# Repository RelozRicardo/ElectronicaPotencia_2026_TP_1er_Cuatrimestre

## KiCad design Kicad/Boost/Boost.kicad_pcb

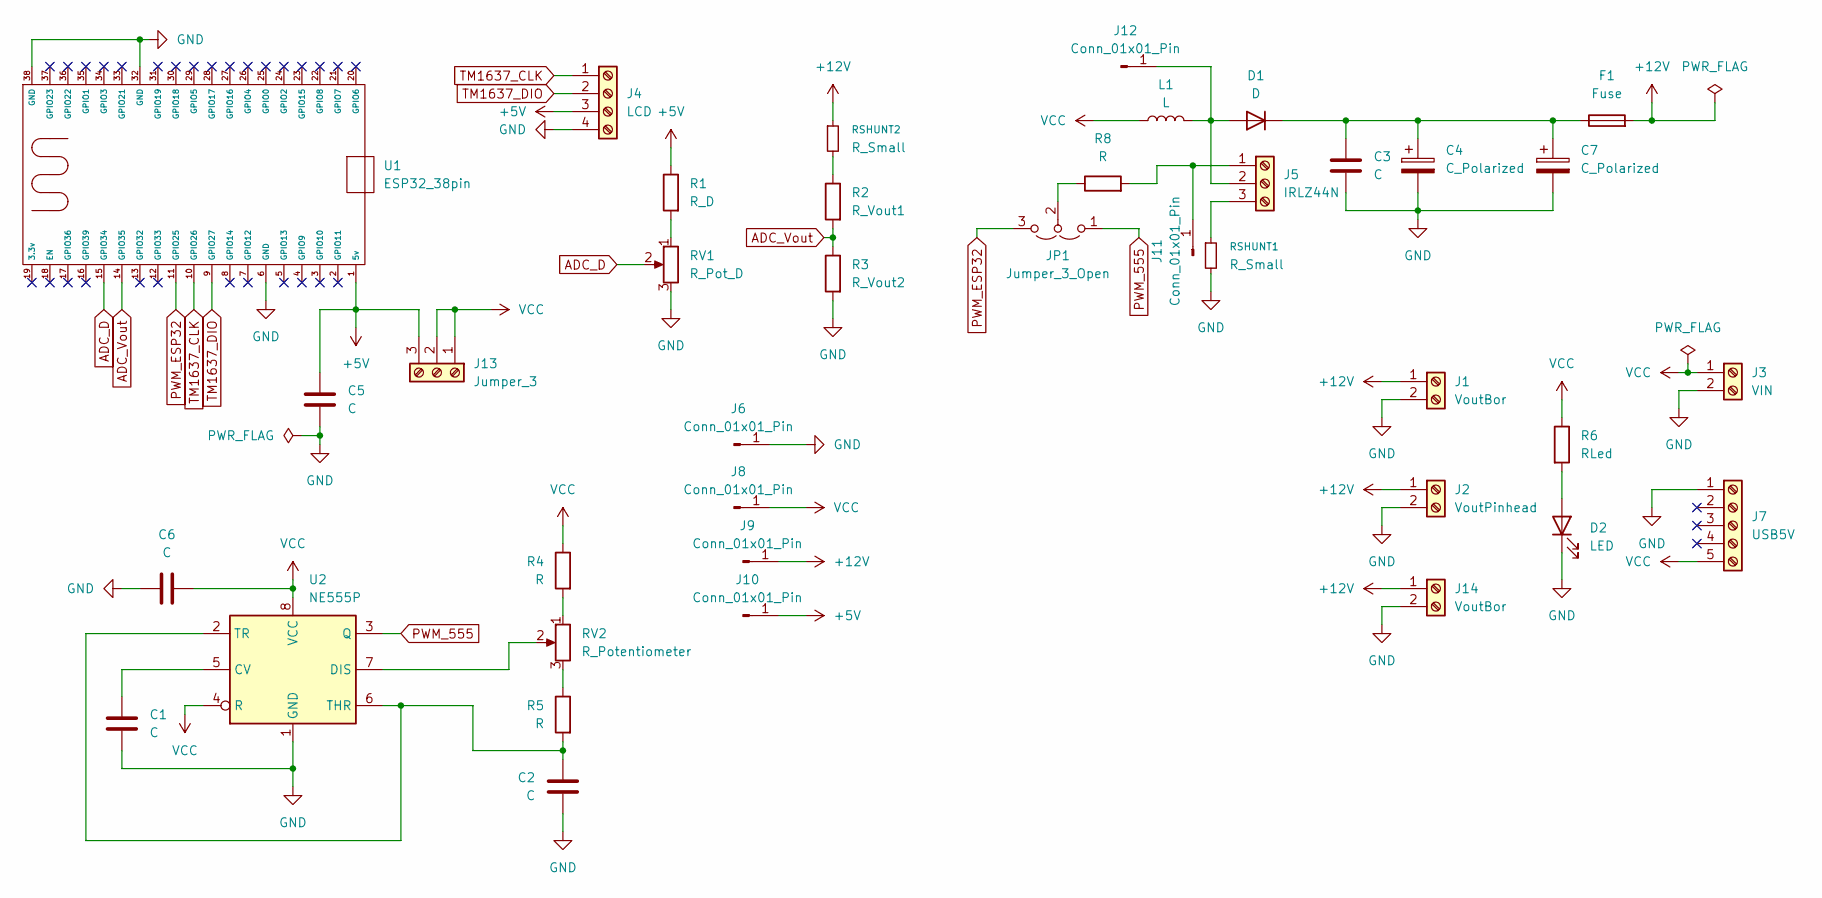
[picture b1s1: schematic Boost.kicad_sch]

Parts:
C1, C2, C3, C5, C6: C; C_Disc_D3.8mm_W2.6mm_P2.50mm
C4, C7: C_Polarized; CP_Radial_D6.3mm_P2.50mm
D1: D; D_DO-201_P12.70mm_Horizontal
D2: LED; LED_D5.0mm
F1: Fuse; Fuse_Bourns_MF-RG400
J1, J14: VoutBor; PhoenixContact_MSTBA_2,5_2-G-5,08_1x02_P5.08mm_Horizontal
J2: VoutPinhead; Molex_KK-254_AE-6410-02A_1x02_P2.54mm_Vertical
J3: VIN; PhoenixContact_MSTBA_2,5_2-G-5,08_1x02_P5.08mm_Horizontal
J4: LCD; PinHeader_1x04_P2.54mm_Vertical
J5: IRLZ44N; TerminalBlock_Xinya_XY308-2.54-3P_1x03_P2.54mm_Horizontal
J6, J8, J9, J10, J11, J12: Conn_01x01_Pin; PinHeader_1x01_P2.54mm_Vertical
J7: USB5V; MicroUsb_Arduino
J13: Jumper_3; PinHeader_1x03_P2.54mm_Vertical
JP1: Jumper_3_Open; PinHeader_1x03_P2.54mm_Vertical
L1: L; Inductor_T94_Vertical
R1: R_D; R_Axial_DIN0207_L6.3mm_D2.5mm_P7.62mm_Horizontal
R2: R_Vout1; R_Axial_DIN0207_L6.3mm_D2.5mm_P7.62mm_Horizontal
R3: R_Vout2; R_Axial_DIN0207_L6.3mm_D2.5mm_P7.62mm_Horizontal
R4, R5, R8: R; R_Axial_DIN0207_L6.3mm_D2.5mm_P7.62mm_Horizontal
R6: RLed; R_Axial_DIN0207_L6.3mm_D2.5mm_P7.62mm_Horizontal
RSHUNT1, RSHUNT2: R_Small; R_2010_5025Metric_Pad1.40x2.65mm_HandSolder
RV1: R_Pot_D; Potentiometer_ACP_CA9-H2,5_Horizontal
RV2: R_Potentiometer; Potentiometer_ACP_CA9-H2,5_Horizontal
U1: ESP32_38pin; ESP32Wroom32_38Pines
U2: NE555P; DIP-8_W7.62mm

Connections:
+5V: C5.1, J4.3, J10.1 (Pin_1_1), J13.3, R1.1, U1.1 (5v)
+12V: F1.2, J1.1, J2.1, J9.1 (Pin_1_1), J14.1, RSHUNT2.1
ADC_D: RV1.2, U1.15 (GPIO34)
ADC_Vout: R2.2, R3.1, U1.14 (GPIO35)
GND: C1.2, C2.2, C3.2, C4.2, C5.2, C6.1, C7.2, D2.1 (K), J1.2, J2.2, J3.2, J4.4, J6.1 (Pin_1_1), J7.1, J14.2, R3.2, RSHUNT1.2, RV1.3, U1.6 (GND), U1.32 (GND), U1.38 (GND), U2.1 (GND)
unnamed: D1.2 (A), J5.2, J12.1 (Pin_1_1), L1.2
unnamed: C3.1, C4.1, C7.1, D1.1 (K), F1.1
unnamed: D2.2 (A), R6.2
unnamed: J5.3, RSHUNT1.1
unnamed: J5.1, J11.1 (Pin_1_1), R8.2
unnamed: JP1.2 (C), R8.1
unnamed: R1.2, RV1.1
unnamed: R2.1, RSHUNT2.2
unnamed: R4.2, RV2.1
unnamed: R5.1, RV2.3
unnamed: C1.1, U2.5 (CV)
unnamed: RV2.2, U2.7 (DIS)
unnamed: C2.1, R5.2, U2.2 (TR), U2.6 (THR)
PWM_555: JP1.1 (A), U2.3 (Q)
PWM_ESP32: JP1.3 (B), U1.11 (GPIO25)
TM1637_CLK: J4.1, U1.10 (GPIO26)
TM1637_DIO: J4.2, U1.9 (GPIO27)
VCC: C6.2, J3.1, J7.5, J8.1 (Pin_1_1), J13.1, J13.2, L1.1, R4.1, R6.1, U2.4 (R), U2.8 (VCC)

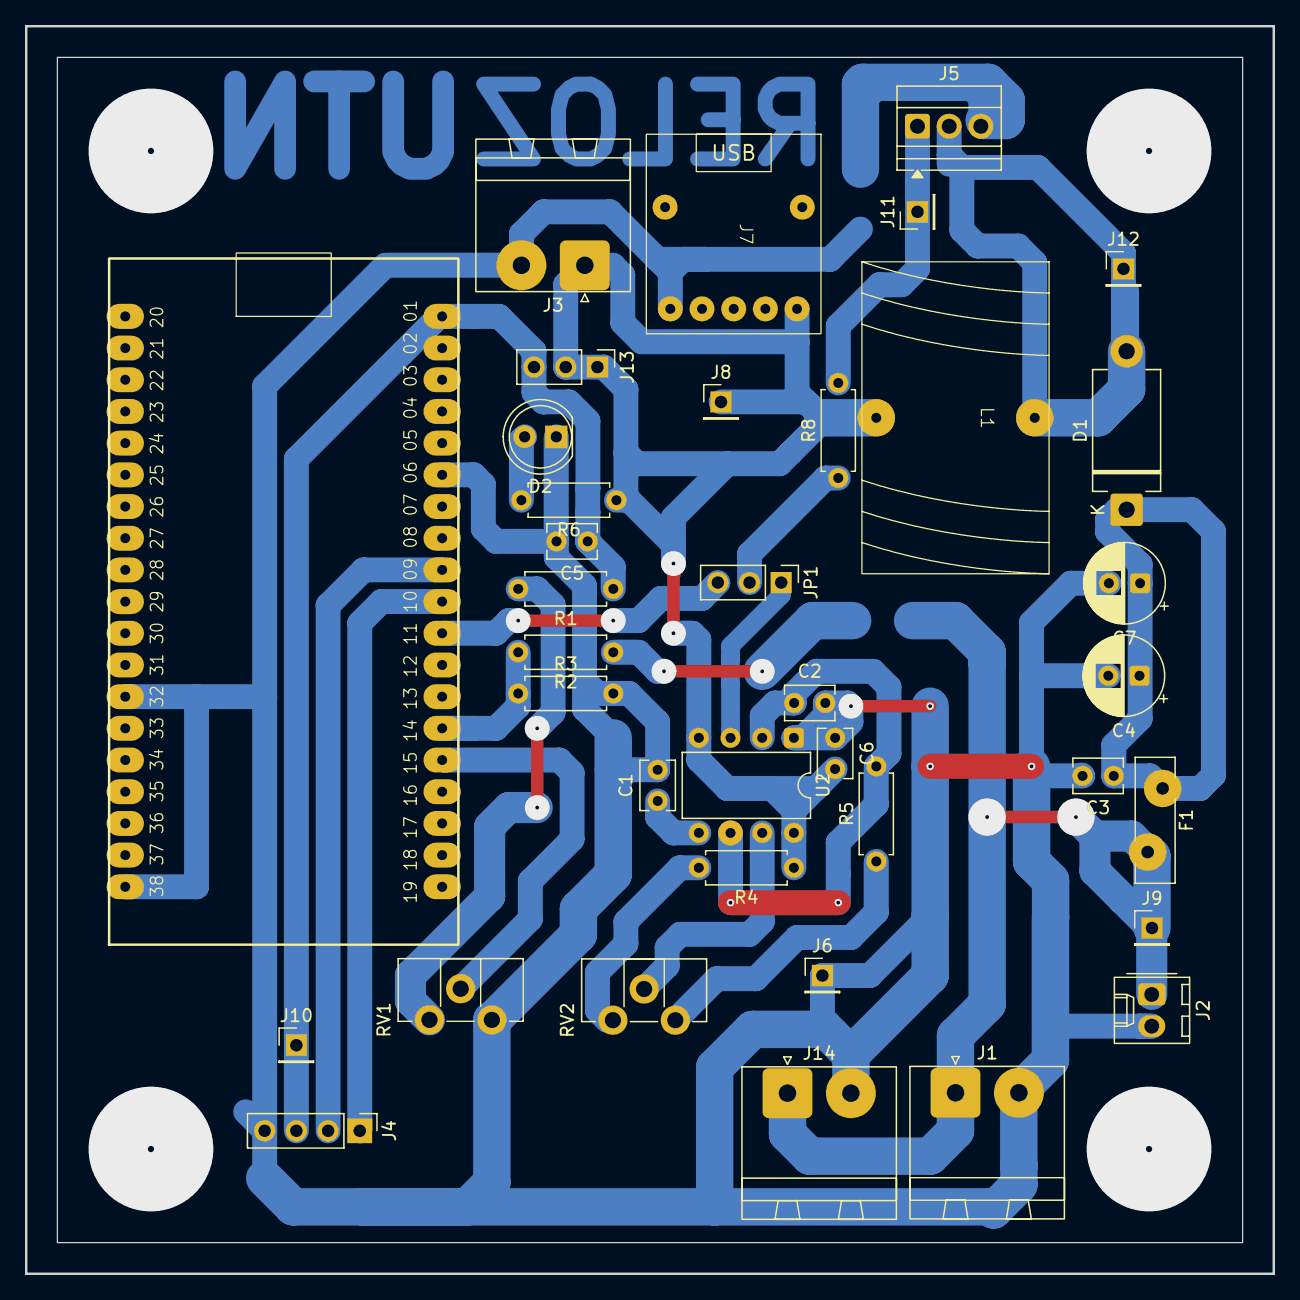
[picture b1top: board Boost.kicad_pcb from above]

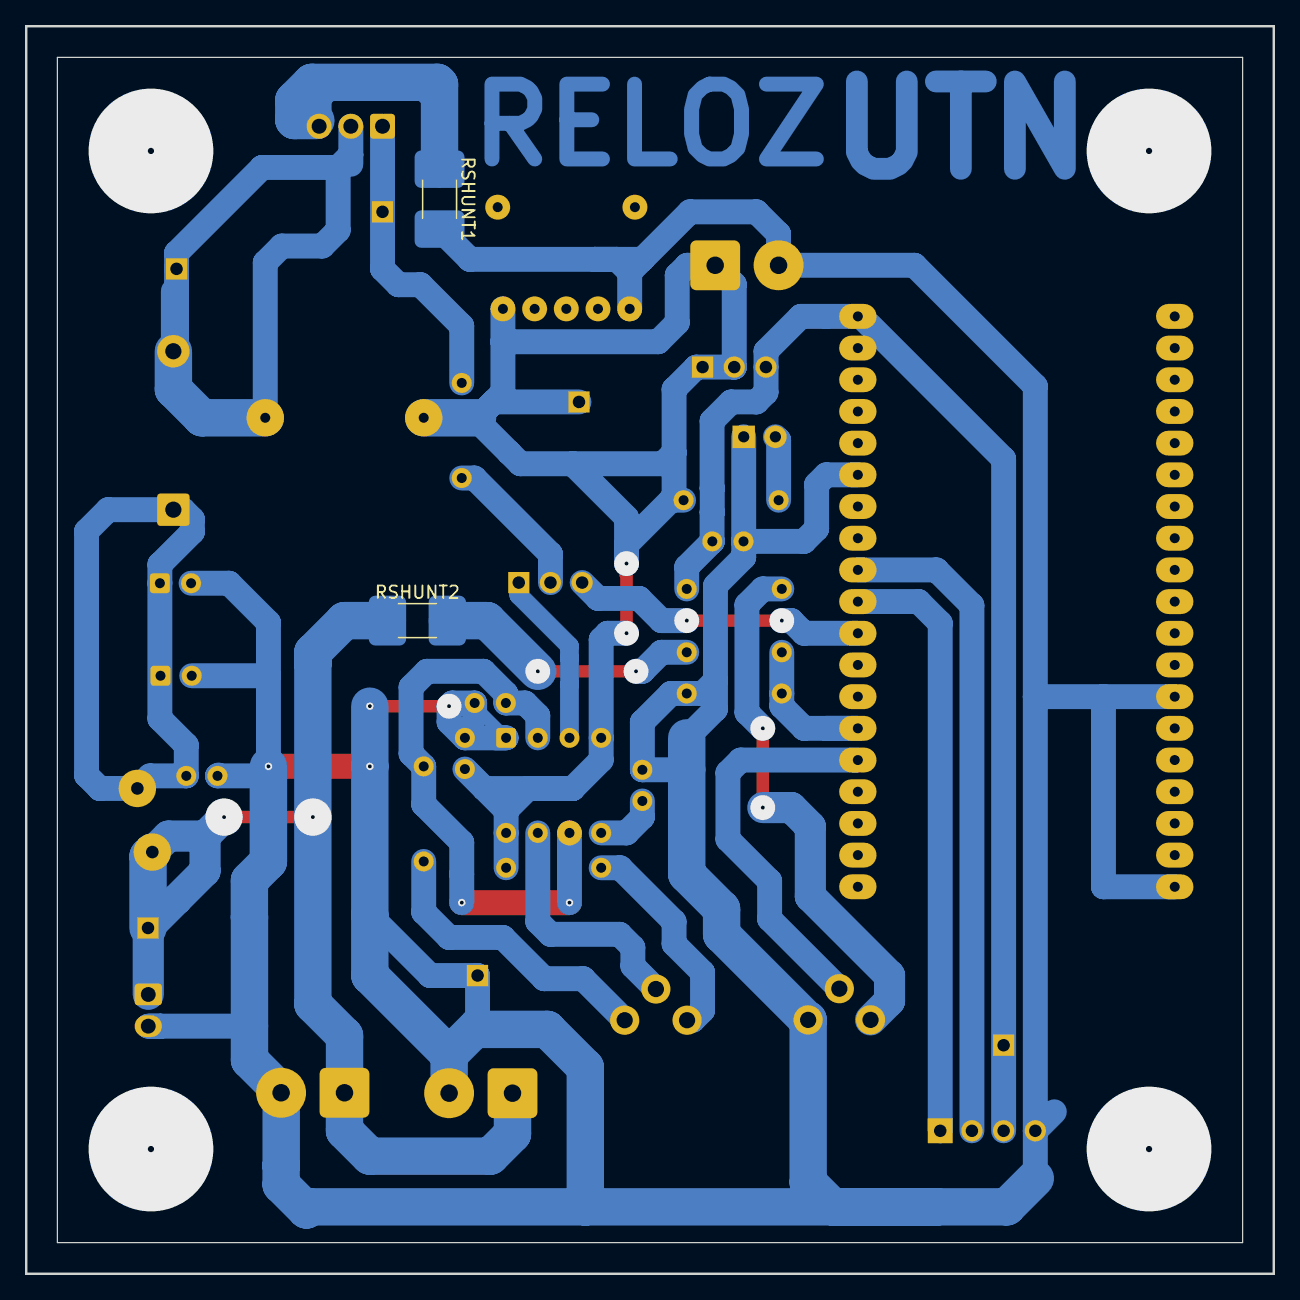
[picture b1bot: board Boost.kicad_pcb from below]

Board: 2 copper layers, 100.0 x 100.0 mm, 39 parts (2 on the bottom side), 23 nets.

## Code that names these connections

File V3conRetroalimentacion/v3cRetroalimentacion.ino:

/*
====================================================
        BOOST CONVERTER CONTROL - ESP32
        Arduino Core 3.3.8
        Board: ESP32 Dev Module
====================================================
GPIO34 -> Potenciómetro (Setpoint)
GPIO35 -> Vout * 0.128
GPIO25 -> PWM 25 kHz
====================================================
*/

//====================== PINES ======================

const int PIN_ADC_SETPOINT = 34;
const int PIN_ADC_VOUT     = 35;
const int PIN_PWM          = 25;

//======================= ADC =======================

const int   ADC_MAX        = 4095;
const float ADC_VREF       = 3.30;

//======================= PWM =======================

const int PWM_FREQ = 25000;
const int PWM_RES  = 10;
const int PWM_MAX  = 1023;

//=================== CONTROL =======================

float dutyActual = 0.583;

const float DUTY_MIN = 0.47;
const float DUTY_MAX = 0.64;

//============== SOFT START =========================

const float DUTY_SOFT_INICIO = 0.05;
const float DUTY_SOFT_FINAL  = 0.47;
const float DUTY_SOFT_PASO   = 0.05;

const int TIEMPO_SOFT = 50;      // ms
const int ESPERA_FINAL = 100;    // ms

//================== TENSIONES ======================

const float VREF_MIN = 10.0;
const float VREF_MAX = 14.0;
const float DIVISOR = 0.128;

//================ REGULACION =======================

const float TOLERANCIA = 0.02;      // ±2 %
const float PASO_DUTY = 0.002;      // 0.2 %
const int TIEMPO_CONTROL = 5;       // ms

//===================================================

void escribirPWM(float duty){
    duty = constrain(duty, DUTY_MIN, DUTY_MAX);
    uint16_t pwm = duty * PWM_MAX;
    ledcWrite(PIN_PWM, pwm);
}

//===================================================

float leerSetpoint(){
    long suma = 0;
    for(int i=0;i<16;i++)
        suma += analogRead(PIN_ADC_SETPOINT);

    int adc = suma / 16;
    return VREF_MIN + ((VREF_MAX - VREF_MIN) * ((float)adc / ADC_MAX));
}

//===================================================

float leerVout(){
    long suma = 0;
    for(int i=0;i<16;i++)
        suma += analogRead(PIN_ADC_VOUT);

    int adc = suma / 16;
    float vPin = adc * ADC_VREF / ADC_MAX;
    return vPin / DIVISOR;
}

//===================================================

void softStart(){
    Serial.println("Soft Start");
    float duty = DUTY_SOFT_INICIO;
    while(duty < DUTY_SOFT_FINAL)
    {
        ledcWrite(PIN_PWM, duty * PWM_MAX);

        Serial.print("Duty: ");
        Serial.print(duty * 100.0,1);
        Serial.println("%");

        delay(TIEMPO_SOFT);

        duty += DUTY_SOFT_PASO;

        if(duty > DUTY_SOFT_FINAL)
            duty = DUTY_SOFT_FINAL;
    }

    dutyActual = DUTY_SOFT_FINAL;
    escribirPWM(dutyActual);
    delay(ESPERA_FINAL);
    Serial.println("Soft Start OK");
}

//===================================================

void setup()
{
    Serial.begin(115200);

    analogReadResolution(12);

    ledcAttach(PIN_PWM, PWM_FREQ, PWM_RES);

    softStart();
}

//===================================================

void loop()
{

    //---------------- Leer referencias ----------------

    float Vref = leerSetpoint();
    float Vout = leerVout();

    //---------------- Tolerancia -----------------------

    float margen = Vref * TOLERANCIA;
    //---------------- Regulación -----------------------

    if(Vout < (Vref - margen)){
        dutyActual += PASO_DUTY;
    }
    else if(Vout > (Vref + margen)){
        dutyActual -= PASO_DUTY;
    }

    dutyActual = constrain(dutyActual, DUTY_MIN, DUTY_MAX);

    escribirPWM(dutyActual);

    //---------------- Monitor Serie -------------------

    Serial.print("Vref: ");
    Serial.print(Vref,2);

    Serial.print(" V");

    Serial.print("    Vout: ");
    Serial.print(Vout,2);

    Serial.print(" V");

    Serial.print("    Duty: ");
    Serial.print(dutyActual*100.0,2);

    Serial.println("%");

    delay(TIEMPO_CONTROL);
}
